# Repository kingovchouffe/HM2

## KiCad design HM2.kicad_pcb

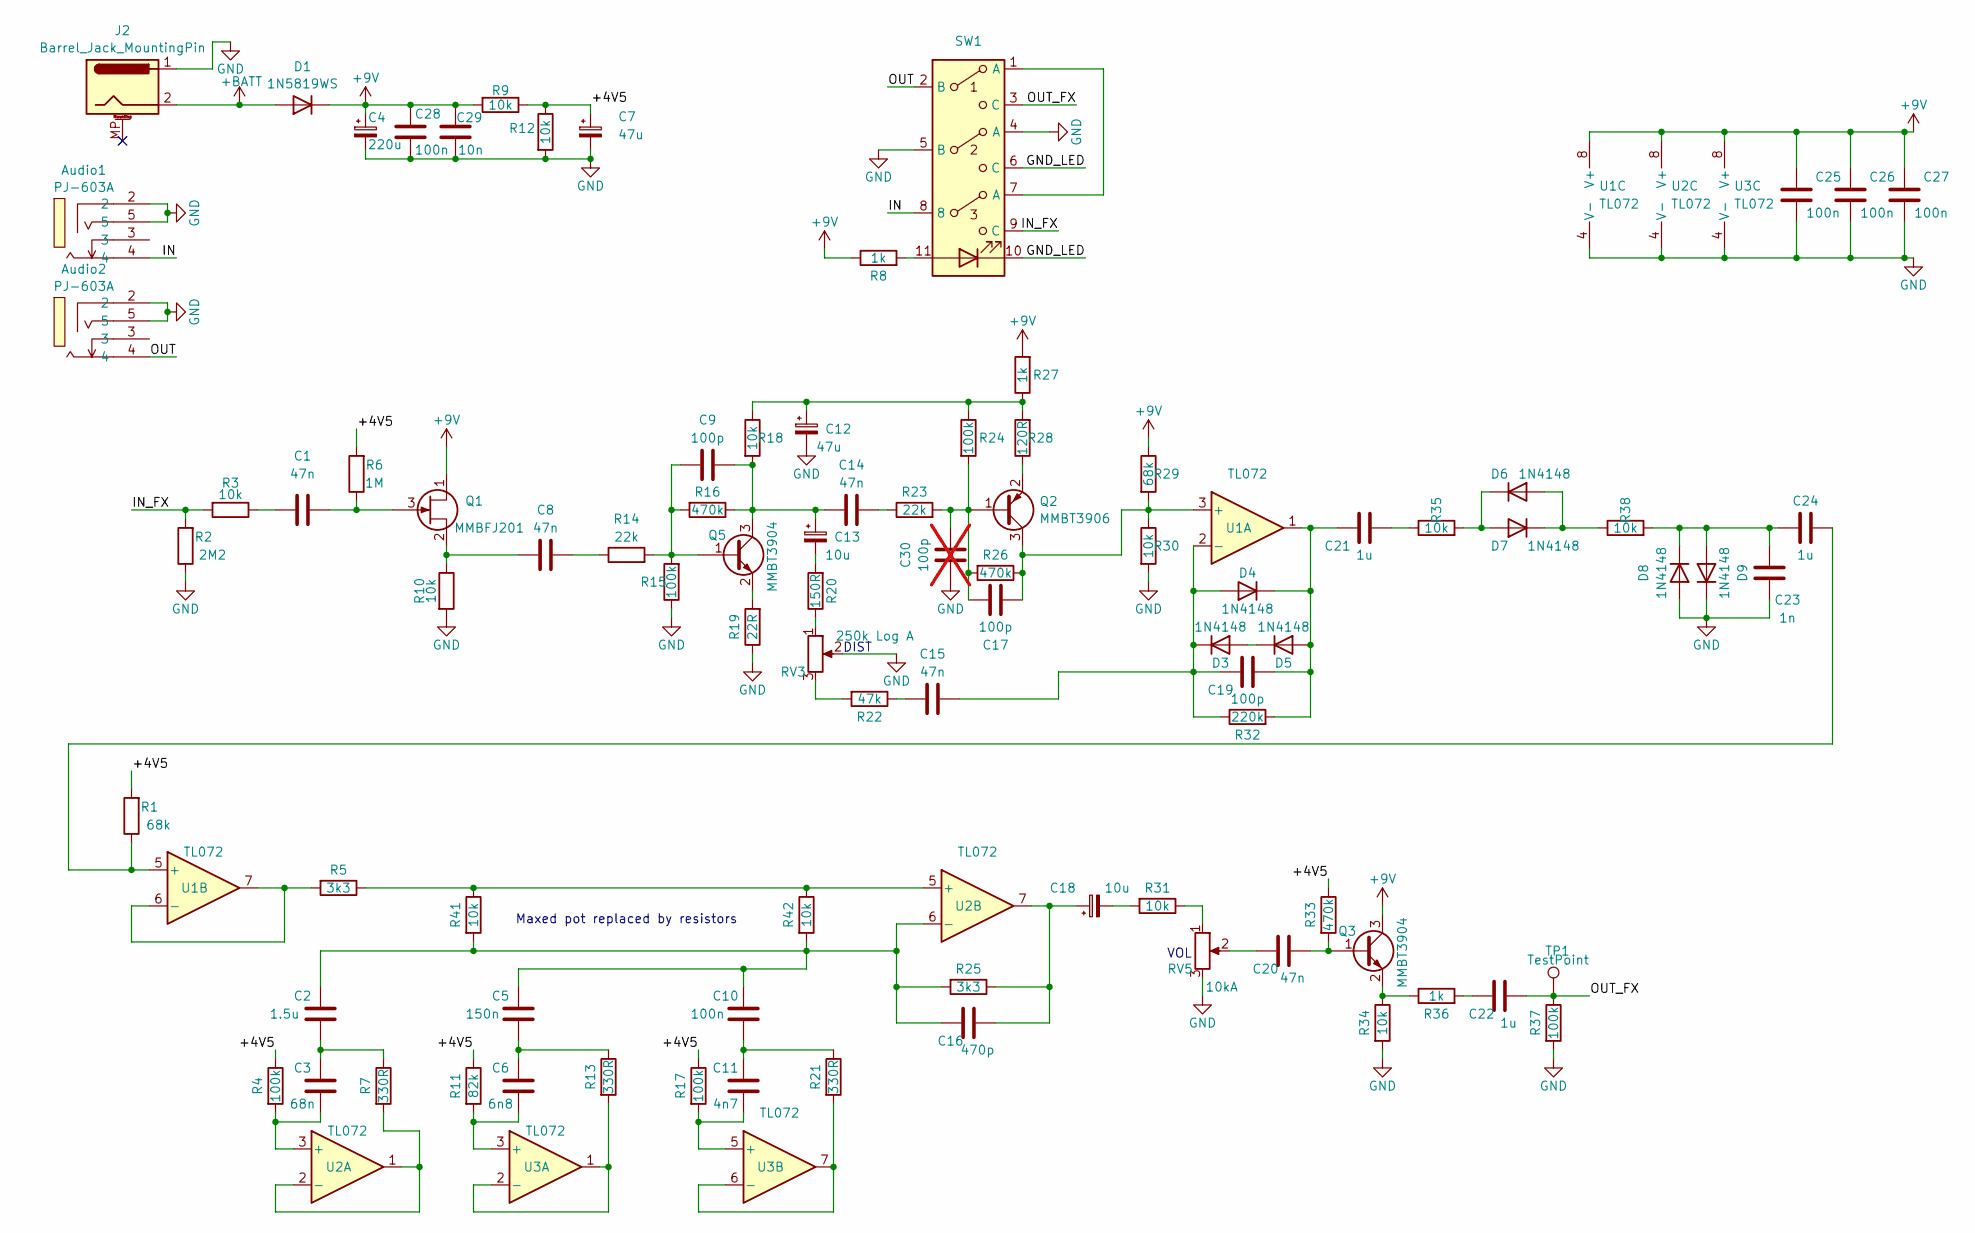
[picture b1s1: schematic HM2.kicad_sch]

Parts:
Audio1, Audio2: PJ-603A; AUDIO-TH_PJ-603A_1; LCSC Part C309273
C1, C8, C14, C15, C20: 47n; C_0603_1608Metric
C2: 1.5u; C_0805_2012Metric
C3: 68n; C_0603_1608Metric
C4: 220u; CP_Elec_6.3x7.7
C5: 150n; C_0603_1608Metric
C6: 6n8; C_0603_1608Metric
C7: 47u; CP_Elec_6.3x5.8
C9, C17, C19: 100p; C_0603_1608Metric
C10, C25, C26, C27, C28: 100n; C_0603_1608Metric
C11: 4n7; C_0603_1608Metric
C12: 47u; CP_Elec_4x5.8
C13, C18: 10u; CP_Elec_5x5.4
C16: 470p; C_0603_1608Metric
C21, C22, C24: 1u; C_0805_2012Metric
C23: 1n; C_0603_1608Metric
C29: 10n; C_0603_1608Metric
C30: 100p; C_0603_1608Metric; not fitted
D1: 1N5819WS; D_SOD-323
D3, D4, D5, D6, D7, D8, D9: 1N4148; D_SOD-323
J2: Barrel_Jack_MountingPin; BarrelJack_Horizontal
Q1: MMBFJ201; SOT-23-3
Q2: MMBT3906; SOT-23
Q3, Q5: MMBT3904; SOT-23
R1, R29: 68k; R_0603_1608Metric
R2: 2M2; R_0603_1608Metric
R3, R9, R10, R12, R18, R30, R31, R34, R35, R38, R41, R42: 10k; R_0603_1608Metric
R4, R15, R17, R24, R37: 100k; R_0603_1608Metric
R5, R25: 3k3; R_0603_1608Metric
R6: 1M; R_0603_1608Metric
R7, R13, R21: 330R; R_0603_1608Metric
R8, R27, R36: 1k; R_0603_1608Metric
R11: 82k; R_0603_1608Metric
R14, R23: 22k; R_0603_1608Metric
R16, R26, R33: 470k; R_0603_1608Metric
R19: 22R; R_0603_1608Metric
R20: 150R; R_0603_1608Metric
R22: 47k; R_0603_1608Metric
R28: 120R; R_0603_1608Metric
R32: 220k; R_0603_1608Metric
RV3: 250k Log A; Potentiometer_Alpha_RD901F-40-00D_Single_Vertical
RV5: 10kA; Potentiometer_Alpha_RD901F-40-00D_Single_Vertical
SW1: 3PDT_LED
TP1: TestPoint; TestPoint_Pad_D1.5mm
U1, U2, U3: TL072; SOIC-8_3.9x4.9mm_P1.27mm

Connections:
+9V: C4.1, C25.2, C26.2, C27.2, C28.2, C29.2, D1.1 (K), Q1.1 (D), Q3.3 (C), R8.1, R9.2, R27.2, R29.1, U1.8 (V+), U2.8 (V+), U3.8 (V+)
+BATT: D1.2 (A), J2.2
/+4V5: C7.1, R1.2, R4.1, R6.2, R9.1, R11.1, R12.1, R17.1, R33.1
/GND_LED: SW1.6 (C), SW1.10, SW1.12
/IN: Audio1.4, SW1.8
/IN_FX: R2.2, R3.2, SW1.9 (C)
/OUT: Audio2.4, SW1.2 (B)
/OUT_FX: C22.1, R37.1, SW1.3 (C), TP1.1
GND: Audio1.2, Audio1.5, Audio2.2, Audio2.5, C4.2, C7.2, C12.2, C23.2, C25.1, C26.1, C27.1, C28.1, C29.1, C30.2, D8.2 (A), D9.1 (K), J2.1, R2.1, R10.2, R12.2, R15.1, R19.1, R30.2, R34.2, R37.2, RV3.2, RV5.3, SW1.4 (A), SW1.5 (B), U1.4 (V-), U2.4 (V-), U3.4 (V-)
unnamed: C1.1, R3.1
unnamed: C2.1, C3.2, R7.1
unnamed: C5.1, C6.2, R13.1
unnamed: C8.2, R14.1
unnamed: C10.1, C11.2, R21.1
unnamed: C12.1, R18.1, R24.1, R27.1, R28.2
unnamed: C13.2, R20.2
unnamed: C14.2, R23.1
unnamed: C15.1, R22.1
unnamed: C16.1, C18.1, R25.1, U2.7
unnamed: C18.2, R31.2
unnamed: C20.2, RV5.2
unnamed: C21.1, R35.1
unnamed: C22.2, R36.2
unnamed: D3.2 (A), D5.1 (K)
unnamed: C15.2, C19.2, D3.1 (K), D4.2 (A), R32.1, U1.2 (-)
unnamed: C19.1, C21.2, D4.1 (K), D5.2 (A), R32.2, U1.1
unnamed: D6.2 (A), D7.1 (K), R38.1
unnamed: D6.1 (K), D7.2 (A), R35.2
unnamed: C23.1, C24.2, D8.1 (K), D9.2 (A), R38.2
unnamed: C1.2, Q1.3 (G), R6.1
unnamed: C8.1, Q1.2 (S), R10.1
unnamed: C17.2, C30.1, Q2.1 (B), R23.2, R24.2, R26.2
unnamed: C17.1, Q2.3 (C), R26.1, R29.2, R30.1, U1.3 (+)
unnamed: Q2.2 (E), R28.1
unnamed: C9.1, Q5.1 (B), R14.2, R15.2, R16.2
unnamed: C9.2, C13.1, C14.1, Q5.3 (C), R16.1, R18.2
unnamed: Q5.2 (E), R19.2
unnamed: R8.2, SW1.11
unnamed: R20.1, RV3.1
unnamed: R22.2, RV3.3
unnamed: R31.1, RV5.1
unnamed: SW1.1 (A), SW1.7 (A)
unnamed: C24.1, R1.1, U1.5 (+)
unnamed: R5.2, U1.6 (-), U1.7
unnamed: C3.1, R4.2, U2.3 (+)
unnamed: R7.2, U2.1, U2.2 (-)
unnamed: R5.1, R41.1, R42.1, U2.5 (+)
unnamed: C2.2, C5.2, C10.2, C16.2, R25.2, R41.2, R42.2, U2.6 (-)
unnamed: C6.1, R11.2, U3.3 (+)
unnamed: R13.2, U3.1, U3.2 (-)
unnamed: C11.1, R17.2, U3.5 (+)
unnamed: R21.2, U3.6 (-), U3.7

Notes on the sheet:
VOL
DIST
Maxed pot replaced by resistors

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
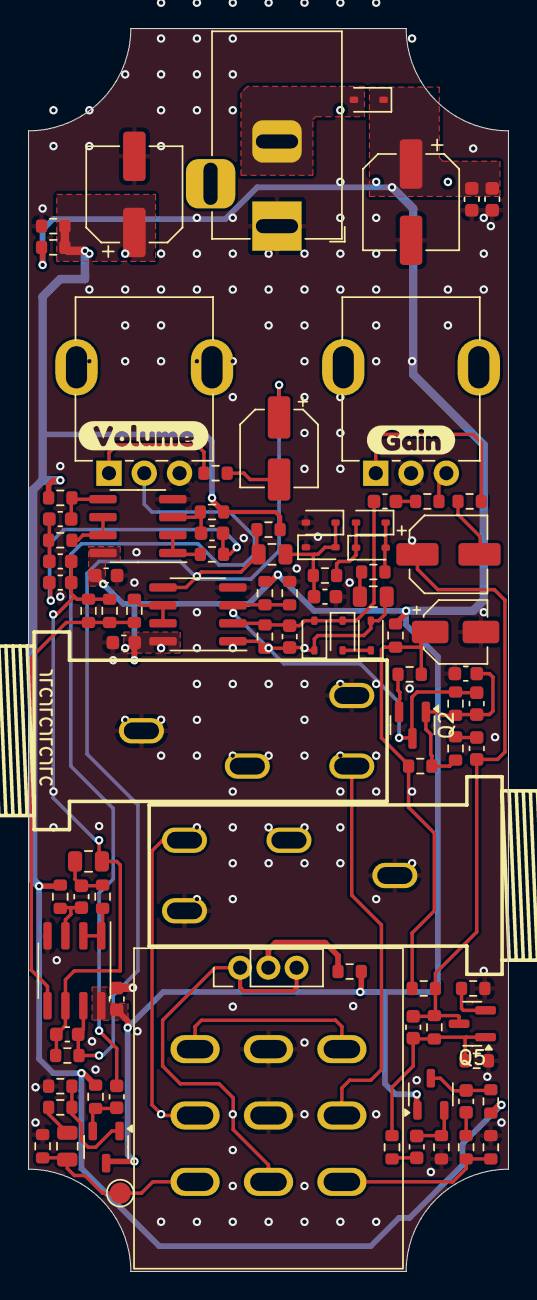
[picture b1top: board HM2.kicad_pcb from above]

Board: 2 copper layers, 34.0 x 88.0 mm, 95 parts (0 on the bottom side), 54 nets.

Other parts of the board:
kibuzzard-66E8676F: G***; kibuzzard-66E8676F
kibuzzard-66E8688E: G***; kibuzzard-66E8688E
kibuzzard-66E86754: G***; kibuzzard-66E86754

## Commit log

2022-08-13 pcb routed
2022-08-13 PCB send to prod
2022-09-27 Schematic revision add decoupling cap on opamp
2024-09-03 v3 to production
2024-09-08 V5 layout to review
2024-09-27 Added mecanical drawing and new pdf schem
    v5 working
2024-09-27 cleaning repos
2025-03-30 add art for the enclosure
